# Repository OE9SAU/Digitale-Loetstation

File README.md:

# Digitale Lötstation mit ATtiny 84 v3

Soldering Unit for Weller RT solder tips.<br>
PCB design by OE9SAU <br>
µC-Code and STL-Desing by OE1CGS [http://www.oe1cgs.at/smd-loetstation/] <br>

v3: Add SK55 for reverse polarity protection

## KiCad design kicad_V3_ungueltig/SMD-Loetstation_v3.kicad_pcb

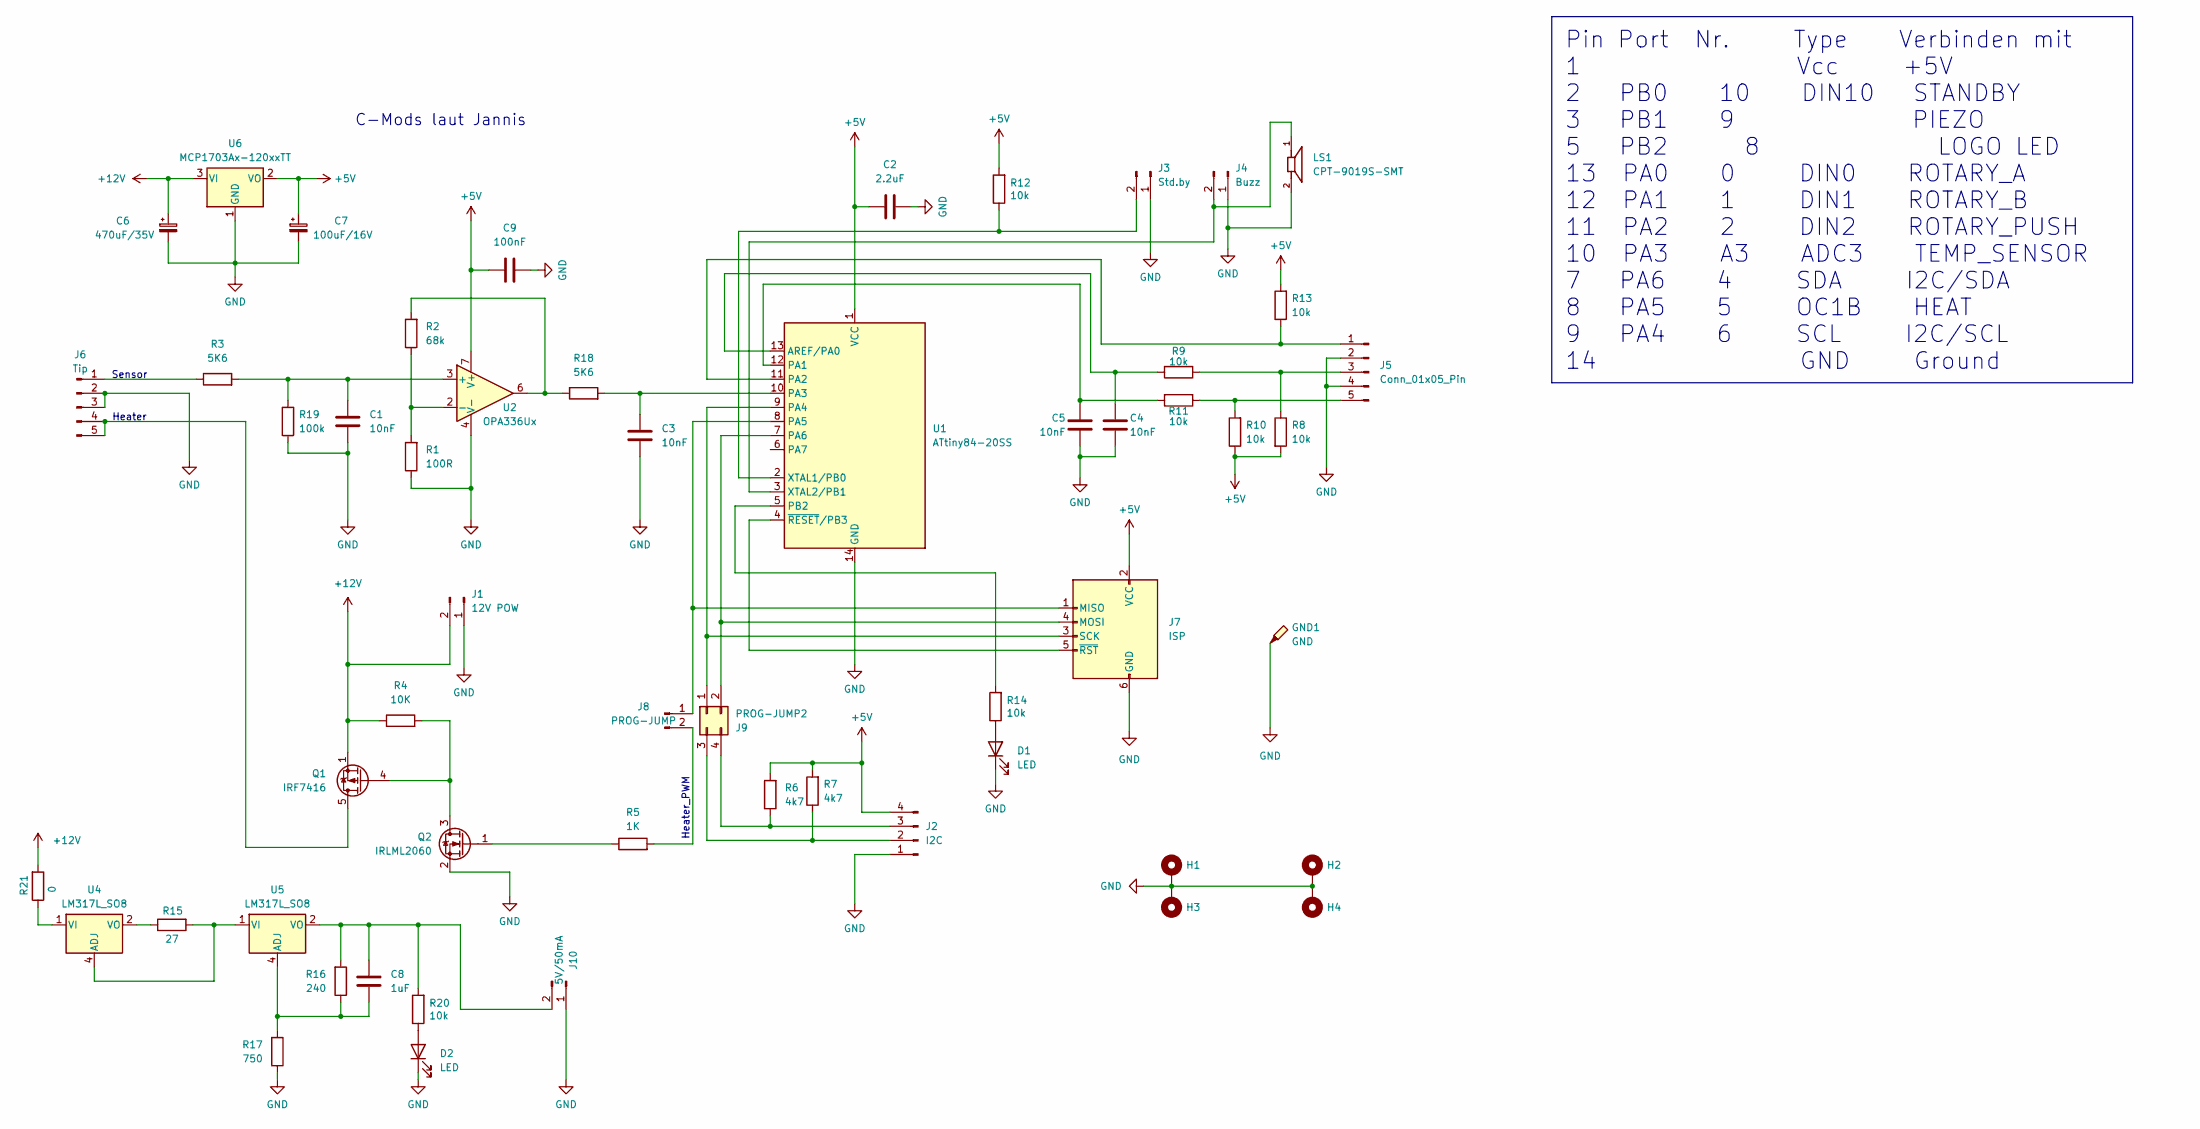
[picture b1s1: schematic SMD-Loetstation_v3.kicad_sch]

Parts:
C1, C3, C4, C5: 10nF; C_0805_2012Metric_Pad1.18x1.45mm_HandSolder
C2: 2.2uF; C_0805_2012Metric_Pad1.18x1.45mm_HandSolder
C6: 470uF/35V; CP_Elec_10x10.5
C7: 100uF/16V; CP_Elec_6.3x5.4
C8: 1uF; C_0805_2012Metric_Pad1.18x1.45mm_HandSolder
C9: 100nF; C_0805_2012Metric_Pad1.18x1.45mm_HandSolder
D1, D2: LED; LED_0805_2012Metric
GND1: GND; TestPoint_Pad_2.0x2.0mm
H1, H2, H3, H4: MountingHole_Pad; MountingHole_2.5mm_Pad
J1: 12V POW; JST_XH_B2B-XH-A_1x02_P2.50mm_Vertical
J2: I2C; PinHeader_1x04_P2.54mm_Vertical
J3: Std.by; PinHeader_1x02_P2.54mm_Vertical
J4: Buzz; PinHeader_1x02_P2.54mm_Vertical
J5: Conn_01x05_Pin; PinHeader_1x05_P2.54mm_Vertical
J6: Tip; JST_XH_B5B-XH-A_1x05_P2.50mm_Vertical
J7: ISP; PinHeader_2x03_P2.54mm_Vertical
J8: PROG-JUMP; PinHeader_1x02_P2.54mm_Vertical
J9: PROG-JUMP2; PinHeader_2x02_P2.54mm_Vertical
J10: 5V/50mA; PinHeader_1x02_P2.54mm_Vertical
LS1: CPT-9019S-SMT; CUI_CPT-9019S-SMT; PART_REV 1.0
Q1: IRF7416; SOIC-8_3.9x4.9mm_P1.27mm
Q2: IRLML2060; SOT-23
R1: 100R; R_0805_2012Metric_Pad1.20x1.40mm_HandSolder
R2: 68k; R_0805_2012Metric_Pad1.20x1.40mm_HandSolder
R3, R18: 5K6; R_0805_2012Metric_Pad1.20x1.40mm_HandSolder
R4: 10K; R_0805_2012Metric_Pad1.20x1.40mm_HandSolder
R5: 1K; R_0805_2012Metric_Pad1.20x1.40mm_HandSolder
R6, R7: 4k7; R_0805_2012Metric_Pad1.20x1.40mm_HandSolder
R8, R9, R10, R11, R12, R13, R14, R20: 10k; R_0805_2012Metric_Pad1.20x1.40mm_HandSolder
R15: 27; R_0805_2012Metric_Pad1.20x1.40mm_HandSolder
R16: 240; R_0805_2012Metric_Pad1.20x1.40mm_HandSolder
R17: 750; R_0805_2012Metric_Pad1.20x1.40mm_HandSolder
R19: 100k; R_0805_2012Metric_Pad1.20x1.40mm_HandSolder
R21: 0; R_0805_2012Metric_Pad1.20x1.40mm_HandSolder
U1: ATtiny84-20SS; SOIC-14_3.9x8.7mm_P1.27mm
U2: OPA336Ux; SO-8_3.9x4.9mm_P1.27mm
U4, U5: LM317L_SO8; SOIC-8_3.9x4.9mm_P1.27mm
U6: MCP1703Ax-120xxTT; SOT-23_Handsoldering

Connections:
+5V: C2.1, C7.1, C9.1, J2.4, J7.2 (VCC), R6.2, R7.2, R8.2, R10.1, R12.2, R13.2, U1.1 (VCC), U2.7 (V+), U6.2 (VO); also elsewhere on the board
+12V: C6.1, J1.2, Q1.1 (S), Q1.2 (S), Q1.3 (S), R4.1, R21.2, U6.3 (VI); also elsewhere on the board
GND: C1.2, C2.2, C3.2, C4.2, C5.1, C6.2, C7.2, C9.2, D1.1 (K), D2.1 (K), GND1.1, H1.1, H2.1, H3.1, H4.1, J1.1, J2.1, J3.1, J4.1, J5.2, J5.4, J6.2, J6.3, J7.6 (GND), J10.1, LS1.2, Q2.2 (S), R1.1, R17.1, R19.1, U1.14 (GND), U2.4 (V-), U6.1 (GND); also elsewhere on the board
unnamed: D1.2 (A), R14.1
unnamed: D2.2 (A), R20.1
unnamed: J2.2, J9.3, R7.1
unnamed: J2.3, J9.4, R6.1
unnamed: J3.2, R12.1, U1.2 (XTAL1/PB0)
unnamed: J4.2, LS1.1, U1.3 (XTAL2/PB1)
unnamed: J5.1, R13.1, U1.11 (PA2)
unnamed: J5.3, R8.1, R9.1
unnamed: J5.5, R10.2, R11.1
unnamed: J6.1, R3.1
unnamed: J6.4, J6.5, Q1.5 (D), Q1.6 (D), Q1.7 (D), Q1.8 (D)
unnamed: J7.1 (MISO), J8.1, U1.8 (PA5)
unnamed: J7.4 (MOSI), J9.2, U1.7 (PA6)
unnamed: J7.3 (SCK), J9.1, U1.9 (PA4)
unnamed: J7.5 (~RST), U1.4 (~RESET/PB3)
unnamed: J8.2, R5.2
unnamed: C8.1, J10.2, R16.2, R20.2, U5.2 (VO), U5.3 (VO), U5.6 (VO), U5.7 (VO)
unnamed: Q1.4 (G), Q2.3 (D), R4.2
unnamed: Q2.1 (G), R5.1
unnamed: R15.1, U4.2 (VO), U4.3 (VO), U4.6 (VO), U4.7 (VO)
unnamed: R2.2, R18.1, U2.6
unnamed: C4.1, R9.2, U1.13 (AREF/PA0)
unnamed: C5.2, R11.2, U1.12 (PA1)
unnamed: C3.1, R18.2, U1.10 (PA3)
unnamed: R14.2, U1.5 (PB2)
unnamed: C1.1, R3.2, R19.2, U2.3 (+)
unnamed: R1.2, R2.1, U2.2 (-)
unnamed: R15.2, U4.4 (ADJ), U5.1 (VI)
unnamed: R21.1, U4.1 (VI)
unnamed: C8.2, R16.1, R17.2, U5.4 (ADJ)

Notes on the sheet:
Pin Port Nr. Type Verbinden mit 1 Vcc +5V 2 PB0 10 DIN10 STANDBY 3 PB1 9 PIEZO 5 PB2 8 LOGO LED 13 PA0 0 DIN0 ROTARY_A 12 PA1 1 DIN1 ROTARY_B 11 PA2 2 DIN2 ROTARY_PUSH 10 PA3 A3 ADC3 TEMP_SENSOR 7 PA6 4 SDA I2C/SDA 8 PA5 5 OC1B HEAT 9 PA4 6 SCL I2C/SCL 14 GND Ground
Heater
Sensor
C-Mods laut Jannis
Heater_PWM

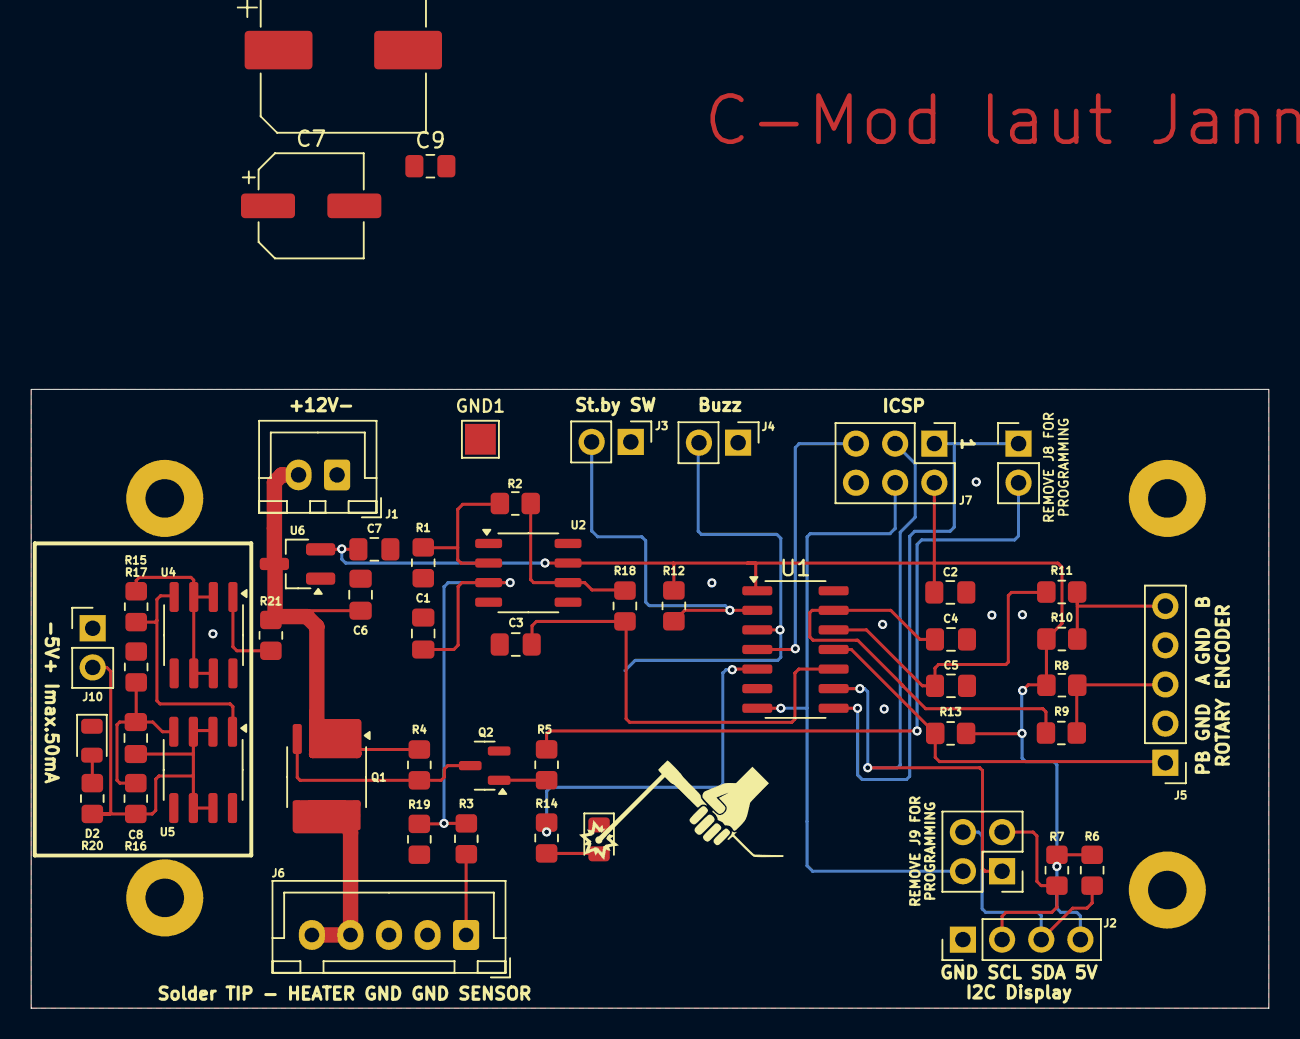
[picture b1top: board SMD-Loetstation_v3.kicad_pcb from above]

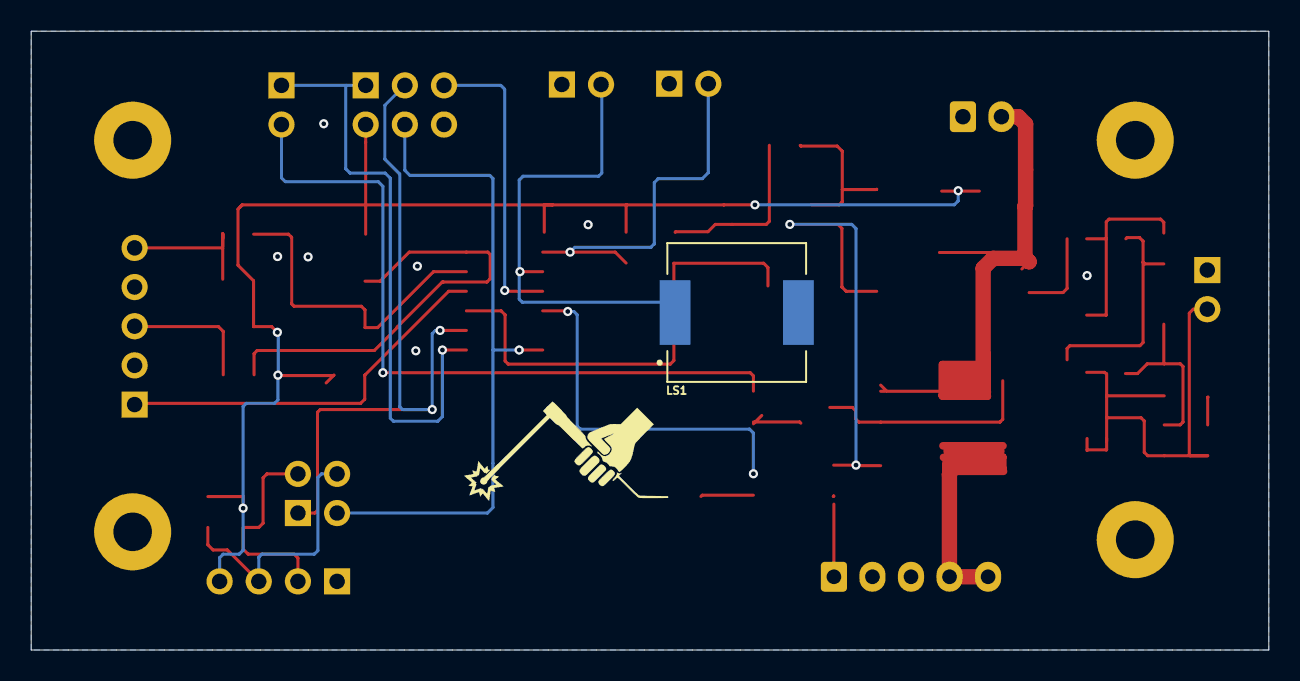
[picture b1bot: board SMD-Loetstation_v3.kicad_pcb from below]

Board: 2 copper layers, 80.3 x 40.1 mm, 59 parts (2 on the bottom side), 33 nets.

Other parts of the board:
C6#2, C7#2: 1uF; C_0805_2012Metric_Pad1.18x1.45mm_HandSolder
G10, G10#2: LOGO

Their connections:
+5V: C7#2.1; also elsewhere on the board
+12V: C6#2.1; also elsewhere on the board
GND: C6#2.2, C7#2.2; also elsewhere on the board

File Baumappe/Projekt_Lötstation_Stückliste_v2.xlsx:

Bezeichner | Footprint | Stückzahl | Bezeichnung
R4,R12,R10,R8,R9,R14,R20,R11,R13 | R_0805_2012Metric_Pad1.20x1.40mm_HandSolder | 9 | 10k
C3,C5,C1,C4 | C_0805_2012Metric_Pad1.18x1.45mm_HandSolder | 4 | 10nF
R3,R18 | R_0805_2012Metric_Pad1.20x1.40mm_HandSolder | 2 | 5K6
R15 | R_0805_2012Metric_Pad1.20x1.40mm_HandSolder | 1 | 27
R17 | R_0805_2012Metric_Pad1.20x1.40mm_HandSolder | 1 | 750
J2 | PinHeader_1x04_P2.54mm_Vertical | 1 | I2C
R21 | R_0805_2012Metric_Pad1.20x1.40mm_HandSolder | 1 | 0
R5 | R_0805_2012Metric_Pad1.20x1.40mm_HandSolder | 1 | 1K
Q2 | SOT-23 | 1 | IRLML2060
R19 | R_0805_2012Metric_Pad1.20x1.40mm_HandSolder | 1 | 100k
J8 | PinHeader_1x02_P2.54mm_Vertical | 1 | PROG-JUMP
J4 | PinHeader_1x02_P2.54mm_Vertical | 1 | Buzz
J7 | PinHeader_2x03_P2.54mm_Vertical | 1 | ISP
U6 | SOT-23_Handsoldering | 1 | MCP1703Ax-120xxTT
U5,U4 | SOIC-8_3.9x4.9mm_P1.27mm | 2 | LM317L_SO8
J1 | JST_XH_B2B-XH-A_1x02_P2.50mm_Vertical | 1 | 12V POW
U2 | SO-8_3.9x4.9mm_P1.27mm | 1 | OPA336Ux
Q1 | SOIC-8_3.9x4.9mm_P1.27mm | 1 | IRF7416
J10 | PinHeader_1x02_P2.54mm_Vertical | 1 | 5V/50mA
R7,R6 | R_0805_2012Metric_Pad1.20x1.40mm_HandSolder | 2 | 4k7
C7,C8,C6 | C_0805_2012Metric_Pad1.18x1.45mm_HandSolder | 3 | 1uF
R2 | R_0805_2012Metric_Pad1.20x1.40mm_HandSolder | 1 | 68k
R1 | R_0805_2012Metric_Pad1.20x1.40mm_HandSolder | 1 | 100R
D1,D2 | LED_0805_2012Metric | 2 | LED
R16 | R_0805_2012Metric_Pad1.20x1.40mm_HandSolder | 1 | 240
GND | TestPoint_Pad_2.0x2.0mm | 1 | GND
J3 | PinHeader_1x02_P2.54mm_Vertical | 1 | Std.by
U1 | SOIC-14_3.9x8.7mm_P1.27mm | 1 | ATtiny84-20SS
J5 | PinHeader_1x05_P2.54mm_Vertical | 1 | Conn_01x05_Pin
J6 | JST_XH_B5B-XH-A_1x05_P2.50mm_Vertical | 1 | Tip
C2 | C_0805_2012Metric_Pad1.18x1.45mm_HandSolder | 1 | 100nF
J9 | PinHeader_2x02_P2.54mm_Vertical | 1 | PROG-JUMP2
LS1 | CUI_CPT-9019S-SMT | 1 | CPT-9019S-SMT

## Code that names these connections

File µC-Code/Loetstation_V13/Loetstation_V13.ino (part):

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   Firmware fuer ATtiny84
   Pin-Belegung:    Pin  Port   Nr.	    Type    Verbinden mit
                     1                  Vcc     +5V
                     2   PB0    10      DIN10   STANDBY
                     3   PB1    9               PIEZO
                    13   PA0    0       DIN0    ROTARY_A
                    12   PA1    1       DIN1    ROTARY_B
                    11   PA2    2       DIN2    ROTARY_PUSH
                    10   PA3    A3      ADC3    TEMP_SENSOR
                     7   PA6    4       SDA     I2C/SDA
                     8   PA5    5       OC1B    HEAT
                     9   PA4    6       SCL     I2C/SCL
                    14                  GND     Ground

                    
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   Version       1.3 vom 19.10.2024 / OE9SAU
                 *Pin-Belegung: 
                  Pin Port Nr.
                   5  PB2  8   LOGO LED
                 *Programmanpassung für LOGO LED
*/

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
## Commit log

2024-10-10 Upload
2024-10-10 Files Update
2024-10-11 Update PCB
2024-10-11 Update pics
2024-10-13 Update PCB 5V
2024-10-13 Update pic´s
2024-10-14 PCB Update
2024-10-14 Update files
2024-10-29 Update v1
    some changings on PCB
2024-10-30 Update MOSFET
2024-10-30 Remove old gerber
2024-10-30 Remove old versions
2024-10-30 Update pic
2024-11-08 Pic Update
2024-11-08 Update Folder
2024-11-08 Add v2_all SMD
2024-11-08 Update Gerber
2025-01-19 Pic v2 update
2025-01-19 Update v2
2025-02-12 Update Repos
2025-03-01 changes V1
2025-03-02 Gitnore
2025-03-02 .gitignore
2025-03-02 GitDate
2025-03-20 Update_Testroutine
2025-03-21 Create Testprogramm_v1
2025-03-21 Upload Code
2025-03-21 Update Code
2025-03-21 Update Code
2025-03-24 Update Test
2025-03-25 stl_v1
2025-03-25 Gitignore
2025-03-25 File reduce
2025-03-25 TestCode_v1
2025-03-25 Update_Testcode_v1
2025-03-25 Info_Aufbau
2025-03-26 Update_Aufbau-Doc
2025-03-26 Test_Code_v2
2025-03-26 Update_Code
2025-04-03 FileUpdate
2025-04-03 Update Baumappe
2025-04-04 uCUpdate
2025-04-04 uC Update
2025-04-13 V15_Beta
2025-04-14 Pic_Update
2025-04-15 Code_Update
2025-04-17 pcb_v3
2025-04-17 no_V3
2025-04-17 Baumappe_update
2025-06-23 PCB v3

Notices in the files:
µC-Code/Loetstation_V13/Loetstation_V13.ino:
Loetstation copyright (C) 2017 OE1CGS Chris
modify it under the terms of the GNU General Public License
